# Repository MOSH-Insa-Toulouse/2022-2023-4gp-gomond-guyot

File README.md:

# Projet Capteur
***
<p align="center">

***

## Sommaire
* [1. Description du projet](#PremiereSection)
* [2. Les livrables](#DeuxiemeSection)
* [3. Matériel nécessaire](#TroisiemeSection)
* [4. Simulation](#QuatriemeSection)
* [5. KiCad](#CinquiemeSection)
  * [5.1. Schématique du circuit et création des symboles et empreintes des composants](#CinquiemeSection1)
  * [5.2. Réalisation du PCB et visualisation 3D](#CinquiemeSection2)
* [6. Fabrication du shield](#SixiemeSection)
  * [6.1. Réalisation du PCB](#SixiemeSection1)
  * [6.2. Perçage et soudure](#SixiemeSection2)
* [7. Arduino](#SeptiemeSection)
  * [7.1. Librairies utilisées](#SeptiemeSection1)
  * [7.2. Code Arduino](#SeptiemeSection2)
* [8. Application Android](#HuigtiemeSection)
* [9. Réalisation des tests et résultats](#NeuviemeSection)
  * [9.1. Banc de test](#NeuviemeSection1)
  * [9.2. Résultats](#NeuviemeSection2)
  * [9.3. Pistes d'améliorations](#NeuviemeSection3)
* [10. Datasheet](#DixiemeSection)
* [Contacts](#OnziemeSection)
 
<div id='PremiereSection'/>

## 1. Description du projet 

Ce projet à lieu dans le cadre de l’UF “Du capteur au banc de test” du département de Génie Physique de l’INSA Toulouse. Basé sur l’article "Pencil Drawn Strain Gauges and Chemiresistor on paper" publié sur Scientific Report en 2014, l’objectif de ce projet est de développer un capteur de déformation low-technologie à base de papier et de graphite. En effet, lorsque l’on déforme le papier, la distance entre les particules de graphite déposées au préalable change selon si l’on applique une tension ou une compression. Cette modification de résistance implique une modification de la conductivité de la couche de graphite. On peut ainsi mesurer une variation de résistance que l’on peut relier à la déformation.
Notre objectif était donc de réaliser ce capteur entièrement, c'est-à-dire que nous allions passer par toutes les étapes de sa conception en partant du design et de la fabrication du PCB jusqu’au test du capteur en passant par de la programmation.

<div id='DeuxiemeSection'/>

## 2. Les livrables
Pour ce projet, nous avions différents livrables à rendre avant le 17/05/2023:
- Un shield PCB fonctionnel connecté à une carte Arduino UNO. Le PCB doit nécessairement contenir un amplificateur transimpédance, un capteur bluetooth, un écran OLED. Il peut également contenir un flex sensor, un potentiomètre digital et un encodeur rotatoir. 
- Un code Arduino permettant de gérer le module bluetooth ainsi que les mesures du capteur de déformation. Si présent sur le shield, le code doit aussi prendre en compte l’écran OLED ainsi que l’encodeur rotatoir. 
- Une application Android APK développée à l’aide du site MIT app inventor. 
- Un protocole de calibration du capteur
- Une datasheet du capteur de déformation développé

Dans notre cas, nous avons choisi d'implémenter en plus du capteur Bluetooth et de l’écran OLED sur notre shield, le flex sensor afin de pouvoir comparer notre capteur avec un capteur industriel et l’encodeur rotatoir afin de pouvoir sélectionner différents modes de mesure pour notre capteur. 

<div id='TroisiemeSection'/>

## 3. Matériel nécessaire 
Pour réaliser le capteur ainsi que le PCB associé, voici la liste des composants nécessaires :

* Résistances : 2 de 1 kOhms, 2 de 10 kOhms, 2 de 100 kOhms
* Capacités : 2 de 100 nF, 1 de 1 uF
* Arduino Uno
* Amplificateur opérationnel LTC1050
* Module Bluetooth HC05
* Encodeur rotatoire KY_040
* Ecran OLED 128x64
* Flex Sensor
 
<div id='QuatriemeSection'/>

## 4. Simulation 
Le but de réaliser en amont la simulation LTSpice du circuit intégré au capteur est de vérifier en théorie qu’il a bien été conçu, c’est-à-dire que l’on a un signal de sortie qui correspond à ce que l’on souhaite avoir pour ensuite pouvoir le traiter à l’aide de l’Arduino UNO. On peut l’utiliser également pour vérifier l’impact des différents composants et déterminer les valeurs de résistances, capacités nécessaires pour avoir la tension de sortie souhaitée. Dans notre cas, n’ayant pas conçu le circuit de nous même, nous avons simplement vérifié à l’aide de LTSpice qu’il correspondait à ce dont nous avions besoin pour réaliser pour amplifier le signal du capteur. La version de LTSpice utilisée version utilisée est LTSpice XVII.

Pour cela, nous avons tout d’abord reproduit le circuit sur LTSpice comme montré ci-dessous:

Nous avons ensuite réalisé deux types de simulation: .tran (qui correspond à un signal transient en entrée du circuit) et .ac (qui correspond à un signal continu en entrée du circuit). La première simulation a pour but de vérifier que le signal en sortie V(ADC) du circuit est suffisamment amplifié pour que l’Arduino UNO puisse mesurer sa valeur. On cherche à avoir une tension de l’ordre du Volt. Le circuit est bien conçu puisqu’on observe sur une simulation de 12s que le signal est amplifié jusqu’à 1 Volt.

La seconde simulation est due à la présence de trois filtres passe-bas dans le circuit visant à réduire les bruits parasitant le signal de sortie. En réalisant une simulation .ac nous pouvons ainsi afficher le diagramme de Bode de chaque filtre passe-bas et afin de trouver les fréquences de coupure des différents filtres. Nous avons d’abord vérifié la fréquence de coupure des différents filtres (de 1,6 Hz, 16 Hz et 1,6 kHz) puis vérifié leur efficacité en réalisant une simulation .ac en introduisant un bruit de 50 Hz.

On observe qu’à 50 Hz, le signal est atténué de 78 dB. Le bruit est donc bien filtré.

<div id='CinquiemeSection'/>

## 5. KiCad 
<div id='CinquiemeSection1'/>

### 5.1. Schématique du circuit et création des symboles et empreintes des composants 
La première étape du KICAD a été de réaliser la schématique du circuit, basé sur la simulation réalisée précédemment. Pour cela, nous avons tout d’abord importé le schéma de l’Arduino Uno qui existe déjà sur KiCAD. Nous avons été ensuite amenés à créer les symboles pour les composants non-existants sur LTSpice, ainsi que leur empreinte sur le PCB. La version de KiCad utilisée est KiCad 7.0. Voici ci-dessous les différentes symboles avec leur empreinte associé:

* Amplificateur LTC1050

* Ecran OLED

* Encodeur rotatoire KY_040

* Module bluetooth HC05

* Flex Sensor

Pour les résistances nous avons choisi comme empreinte la Resistor_THT:R_Axial_DIN0204_L3.6mm_D1.6mm_P5.08mm_Horizontal, excepté pour R2 pour laquelle nous avons pris la même empreinte mais à la verticale (elle a donc été placée à la japonaise). Concernant les capacités, C1 et C2 possède comme empreinte Capacitor_THT: C_Disc_D3.0mm_W1.6mm_P2.50mm, tandis que C4 a pour empreinte Capacitor_THT:C_Rect_L7.0mm_W4.5mm_P5.00mm.

Voici ci-dessous le schéma de la schématique du circuit réalisé sur KiCAD:

<p align="center">

<div id='CinquiemeSection2'/>

### 5.2. Réalisation du PCB et visualisation 3D 
Pour le PCB, nous avions pour contrainte de n’imprimer que sur une seule face. Il a donc fallu optimiser autant que possible les connexions entre les différents composés afin de limiter la présence de PADs. Nous avons réussi à n’avoir besoin que d'un seul PAD sur notre PCB, qui, n’ayant pas de face arrière, s’est traduit par la connexion du PAD à l’aide d’un fil de résistance. Voici ci-dessous l’empreinte du PCB réalisé:

<p align="center">

Le plan en bleu est le plan de masse. Les PADS sont de formes circulaires de 2mm de diamètre avec une forme de perçage circulaire de 1mm pour l’Arduino et le capteur de déformation et 0,8mm pour le reste. Les largeurs de pistes sont de 1mm et l’isolation entre les pistes et le plan de masse est de 0,3mm. Nous avons choisi ces derniers paramètres afin de faciliter l’étape de soudure.
	
Afin de visualiser en 3D notre composant et pouvoir voir la place que prend chaque composant, nous avons dû, pour les empreintes que nous avons créées, utiliser le site internet GrabCADafin de récupérer le fichier 3D de nos composants. Voici-ci dessous la visualisation 3D du PCB réalisé: 
	
<p align="center">

<div id='SixiemeSection'/>

## 6. Fabrication du shield 
<div id='SixiemeSection1'/>

### 6.1. Réalisation du PCB 

Le PCB a été réalisé par Catherine CROUZET du département du Génie Physique de l’INSA Toulouse à l’aide du matériel du département du Génie Physique et du département	Électrique et Informatique. Avant impression, l’empreinte du PCB a été vérifiée par Mme CROUZET qui a ensuite imprimé sur papier le calque de modélisation issu du PCB réalisé sur KiCAD.
 Nous sommes parti d’une plaquette d'époxy couverte d’une couche de cuivre d’environ  60µm sur laquelle nous avons appliqué notre calque qui a permis de tracer les pistes sur la plaquette du PCB à l’aide d’une insolation UV. Une fois les pistes tracées, elles sont ensuite révélées à l’aide d’un révélateur qui après quelques minutes, retire la résine non éclairée pas les UV. La plaquette est ensuite placée dans un bain de perchlorure de fer pendant 7 minutes afin de réaliser la gravure du PCB. Lors de cette étape, le cuivre non protégé par la résine est retiré. Nous obtenons alors le PCB comme désigné sur KiCAD. On applique pour terminer un peu d’acétone afin de retirer les dernières traces de résines encore présentes.

 <div id='SixiemeSection2'/>

### 6.2. Perçage et soudure 
Une fois les pistes du PCB créées, il faut réaliser le perçage du PCB puis la soudure des composants. Pour cela nous avons utilisé la perceuse électrique mise à disposition aux étudiants du Génie Physique. Les tailles de forêts ont été choisies en fonction des tailles de trous de perçage designé sur KiCAD (c’est à dire 0,8mm ou 1mm de diamètre selon les composants). Une fois tous les composants soudés sur la face avant, nous avons pu connecter le PCB à l’Arduino Uno. 

<div id='SeptiemeSection'/>

## 7. Arduino 
<div id='SeptiemeSection1'/>

### 7.1. Librairies utilisées 
Nous avons utiliser la vertion de Arduino IDE 2.1.0.
Pour la réalisation du code Arduino nous avons utiliser deux librairies qui sont **"SoftwareSerial.h"** pour réaliser un software serial sur deux pin pour l'utilisation du modude bluetooth. La deuxième est **"Adafruit_SSD1306.h"** qui sert pour l'utilisation de l'écran OLED.

<div id='SeptiemeSection2'/>

### 7.2. Code Arduino 
Nous avons réaliser deux code Arduino dans ce projet. Le premier permet de controler le capteur et tout ces composants. Le deuxième sert lors de la procédure de calibration.

#### Code pour le Capteur 
Ce [code](https://github.com/MOSH-Insa-Toulouse/2022-2023-4gp-gomond-guyot/blob/main/arduino/Programme_finaleVFinale.ino) est le coeur du fonctionnement du capteur. 
-Il permet tout d'abord récupérer les valeurs de tension en sortie de l'amplificateur et de réaliser les différents calculs pour retrouver la résistance de notre capteur.
-Il permet également le contrôle et l'utilisaton des différents éléments ajoutés sur le shield:
	
   * il y a le **module Bluetooth** qui permet d'envoyer la valeur de tension lue et de l'envoyer à l'application Android.
	
   * il y a **l'encodeur rotatoir** où nous avons grâce à lui réaliser trois menus en fonction d'où l'on se trouve dans la plage de valeurs de l'encodeur. Il y a un menu avec un mode de lecteur continu de la résistance, un autre mode qui réalise une moyenne sur 200 valeurs de la résistance et n mode pour afficher la lecture du flex sensor. Tout ces menus sont visible sur l'écran OLED.
	
   * il y a **l'écran OLED** qui permet d'afficher la valeur de la résistance de notre capteur ou du flex sensor en fonction du menu que nous avons choisi. Le menu où nous sommes est également affiché.

#### Code pour la calibration
Ce [code](https://github.com/MOSH-Insa-Toulouse/2022-2023-4gp-gomond-guyot/blob/main/arduino/programme_calibration.ino) permet de contrôler un Servo-Moteur qui va se positionner à différent angles déterminés (0, 30, 60, 90, 120). Il va attendre 2 secondes à chaques position pour nous permettre de lire la valeur. La procédure est activée grâce à un bouton poussoir et pendant que le servo-moteur est en mouvement une LED est allumée.

<div id='HuigtiemeSection'/>

## 8. Application Android 
Nous avons développé une application Android fonctionnant à l’aide du module Bluetooth HC-05. L’application se présente comme ci-dessous: 

<p align="center">

L’application possède un menu de sélection bluetooth permettant de choisir à quel module bluetooth se connecter. Une fois connecté, le code Arduino envoie via le module la valeur de tension en sortie du circuit V(ADC) en Volt sous forme d’un byte à l’application. L’application convertit ces valeurs tout d’abord en float, puis en résistance en M𝛺 à l’aide de la formule: 

<p align="center">
	
Le schéma fonctionnel du programme derrière l’application est visible sous ce lien: [LIEN APK](https://github.com/MOSH-Insa-Toulouse/2022-2023-4gp-gomond-guyot/blob/main/app/Application_Projet.aia)

<div id='NeuviemeSection'/>

## 9. Réalisation des tests et résultats 
<div id='NeuviemeSection1'/>

### 9.1. Banc de test 
Pour réaliser les différents tests de calibration nous avons réaliser deux bancs de tests pour avoir une calibration en fonction de la déformation et en fonction de l'angle. Nous avons réaliser les deux calibrations car nous avons trouvé, sur le point physique, intéressant de la réaliser en fonction de la déformation de la couche de graphite. Mais sur l'aspect utilisation du capteur, il est plus utile et intéressant de connaitre la résistance en fonction de l'angle que fait le capteur.

#### Banc de test pour la calibration en fonction de la deformation
Pour cette methode nous avons découpé des cercles de différents rayons de courbure (1, 2, 4 et 6 cm) comme montrée ci dessous.

<p align="center">
	
Ce rayon de courbure nous permet de remonter à la déformation ε gracce à la formule suivante qui est expliqué par le shéma ci-dessous.

#### Banc de test pour la calibration en fonction de l'angle
Pour cette methode nous avons utilisé un module en bois  qui était fournis par le département ainsi qu'un servo-moteur. Nous utilisons le code décrit à la partie 7.2 pour la calibration. Le servo-moteur tord le capteur à différents angles prédéfinis.

<div id='NeuviemeSection2'/>

### 9.2. Résultats
Les résultats complets ont été réalisé sur Exel dans le dossier [result.](https://github.com/MOSH-Insa-Toulouse/2022-2023-4gp-gomond-guyot/blob/main/result/calcules_deformation.xlsx) Sinon voici les différentes courbes de calibration en fonction de l'angle et de la déformation.
Nous avons réalisé les mesures en fonction de la déformation en compression et en tension. Pour les mesures en fonction de l'angle, nous avons réalisé seulement la compression car les résultats que nous avons obtenu en tension n'était pas exploitables.

* Variation de la résistance en fonction de la deformation (tension)

* Variation de la résistance en fonction de la deformation (compression)

* Variation de la résistance en fonction de l'angle (compression)

Quand nous travaillons en tension, la monocouche de graphite déposé sur le papier va s'étirer ce qui va augmenter la distance entre les différents atomes de Carbone et ainsi augmenter la résitance du capteur.
Lorsque nous travaillons en tension, il se passe l'opposé. Les atomes de Carbone vont se rapprocher et la résistance du capteur va diminuer.
En fonction du type de crayon utilisé, les variations relatives de résistance changent. En effet, plus le crayon est gras, c'est à dire qu'il dépose plus de graphite, moins sa variation relative de résistance est élevée. Nous pouvons vérifier cela sur les différentes courbes que nous avons obtenu.

<div id='NeuviemeSection3'/>
 
### 9.3. Pistes d'améliorations
Plusieurs pistes d’améliorations pour ce capteur sont possibles. Tout d’abord, comme nous avons pu l’expérimenter, la répétabilité du capteur est peu fiable dû à plusieurs facteurs:

-Le dépôt de la quantité de graphite n’est pas contrôlée, et cette quantité diminue au cours du temps avec l’air alentour.

-Le papier s’use assez rapidement et ne peut pas supporter des déformations trop importantes.

Ainsi, on pourrait essayer de réaliser une méthode afin de déposer une quantité contrôlée de graphite sur le papier, ainsi que choisir un papier plus élastique. 
Un autre ajout possible sur la partie hardware du capteur serait le potentiomètre digital qui permettrait d’adapter la tension de sortie du capteur en fonction de la résistance du capteur. 
La partie banc de tests pourrait être améliorée en réalisant des tests sur des cylindres solides imprimés en 3D et avec plus de tailles différentes afin d’obtenir plus de données pour tracer nos courbes.

#### Comparaison avec le Flex-Sensor SEN-10264

*Variation de la résistance du flex sensor en compression

Pour comparer la sensibilité des deux capteurs, nous pouvons comparer les coefficients directeur du flex sensor avec celui du capteur de contrainte HB sur la compression. Pour le flex sensor, nous avons obtenu un coefficient de -2.27/° tandis que pour le capteur de contrainte HB nous avons -0.24/°. On peu donc dire que le flex sensor est beaucoup plus sensible à la déformation que notre capteur de contrainte en graphite. Le flex sensor pourrait être plus utile pour detecter de petites déformations grâce à sa plus grande sensibilité. A coté de cela, notre capteur en graphite à plus de difficulté à détecter les petites déformation où les petit angles. Il serait plus utile pour savoir s'il est plié ou non.

<div id='DixiemeSection'/>

## 10. Datasheet
La datasheet du capteur est disponible [ici](https://github.com/MOSH-Insa-Toulouse/2022-2023-4gp-gomond-guyot/blob/main/Datasheet.pdf)

<div id='OnziemeSection'/>

## Contacts 
Nous sommes disponibles pour toute question sur le projet, n'hesitez pas à nous contacter.

-GUYOT Adrien : aguyot@etud.insa-toulouse.fr

-GOMOND François : fgomond@insa-toulouse.fr

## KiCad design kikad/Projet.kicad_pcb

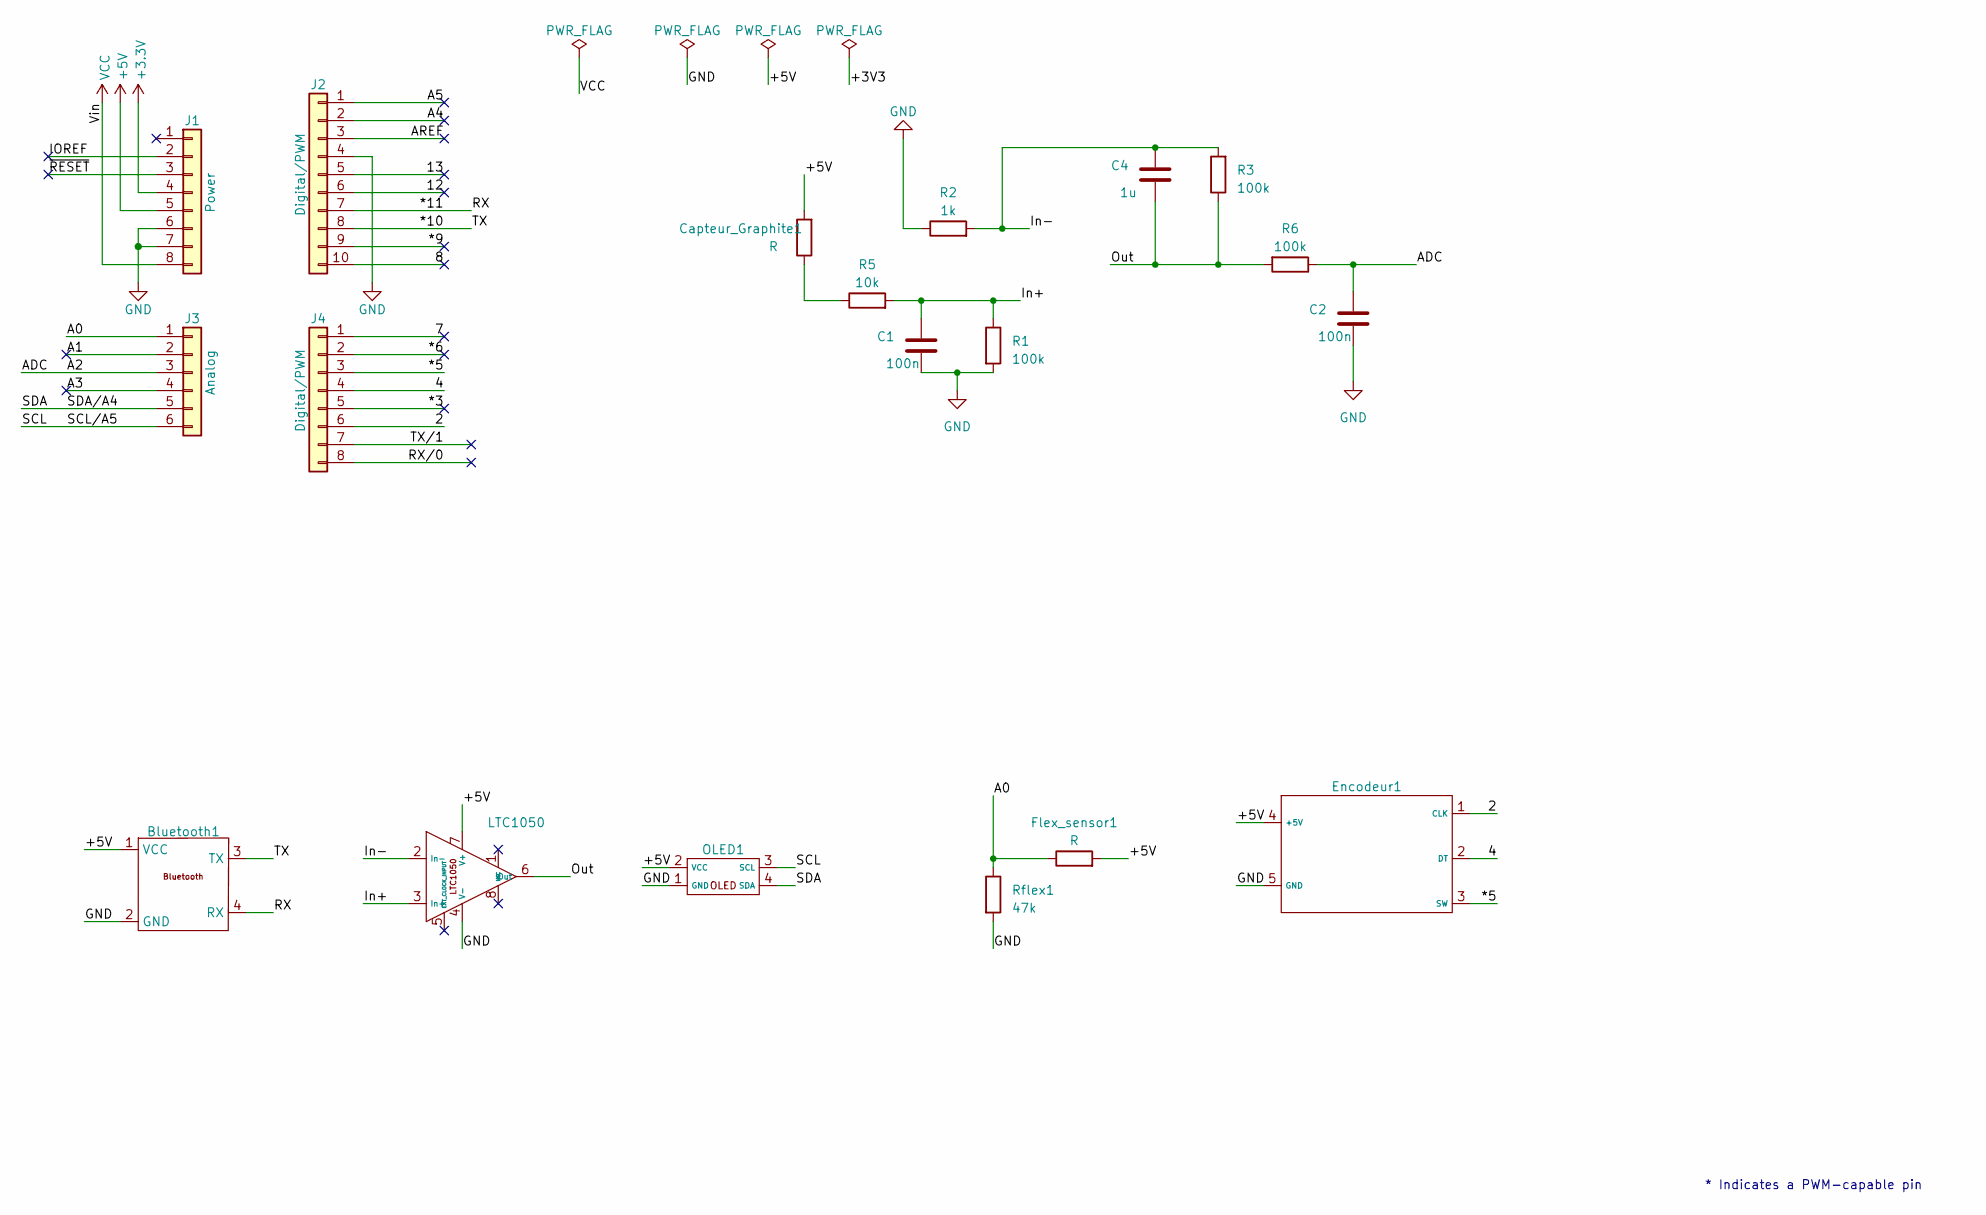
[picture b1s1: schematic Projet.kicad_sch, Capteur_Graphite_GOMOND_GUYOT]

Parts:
Bluetooth1: Bluetooth
C1, C2: 100n; C_Disc_D3.0mm_W1.6mm_P2.50mm
C4: 1u; C_Rect_L7.0mm_W4.5mm_P5.00mm
Capteur_Graphite1: R; PinSocket_1x02_P2.54mm_Vertical
Encodeur1: Encodeur
Flex_sensor1: R; PinSocket_1x02_P2.54mm_Vertical
J1: Power; PinSocket_1x08_P2.54mm_Vertical
J2: Digital/PWM; PinSocket_1x10_P2.54mm_Vertical
J3: Analog; PinSocket_1x06_P2.54mm_Vertical
J4: Digital/PWM; PinSocket_1x08_P2.54mm_Vertical
LTC1050: LTC1050
OLED1: OLED
R1, R3, R6: 100k; R_Axial_DIN0204_L3.6mm_D1.6mm_P5.08mm_Horizontal
R2: 1k; R_Axial_DIN0204_L3.6mm_D1.6mm_P2.54mm_Vertical
R5: 10k; R_Axial_DIN0204_L3.6mm_D1.6mm_P5.08mm_Horizontal
Rflex1: 47k; R_Axial_DIN0204_L3.6mm_D1.6mm_P5.08mm_Horizontal

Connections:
+3V3: J1.4
+5V: Bluetooth1.1 (VCC), Capteur_Graphite1.2, Encodeur1.4 (+5V), Flex_sensor1.2, J1.5, LTC1050.7 (V+), OLED1.2 (VCC)
/2: Encodeur1.1 (CLK), J4.6
/4: Encodeur1.2 (DT), J4.4
/7: J4.1
/8: J2.10
/12: J2.6
/13: J2.5
/*3: J4.5
/*5: Encodeur1.3 (SW), J4.3
/*6: J4.2
/*9: J2.9
/*10: Bluetooth1.3 (TX), J2.8
/*11: Bluetooth1.4 (RX), J2.7
/A0: Flex_sensor1.1, J3.1, Rflex1.1
/A1: J3.2
/A2: C2.2, J3.3, R6.1
/A3: J3.4
/A4: J2.2
/A5: J2.1
/AREF: J2.3
/IOREF: J1.2
/In+: C1.2, LTC1050.3 (In+), R1.1, R5.2
/In-: C4.2, LTC1050.2 (In-), R2.2, R3.2
/Out: C4.1, LTC1050.6 (Out), R3.1, R6.2
/RX/0: J4.8
/SCL: J3.6, OLED1.3 (SCL)
/SDA: J3.5, OLED1.4 (SDA)
/TX/1: J4.7
/~RESET: J1.3
GND: Bluetooth1.2 (GND), C1.1, C2.1, Encodeur1.5 (GND), J1.6, J1.7, J2.4, LTC1050.4 (V-), OLED1.1 (GND), R1.2, R2.1, Rflex1.2
unnamed: Capteur_Graphite1.1, R5.1
VCC: J1.8

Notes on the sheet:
* Indicates a PWM-capable pin

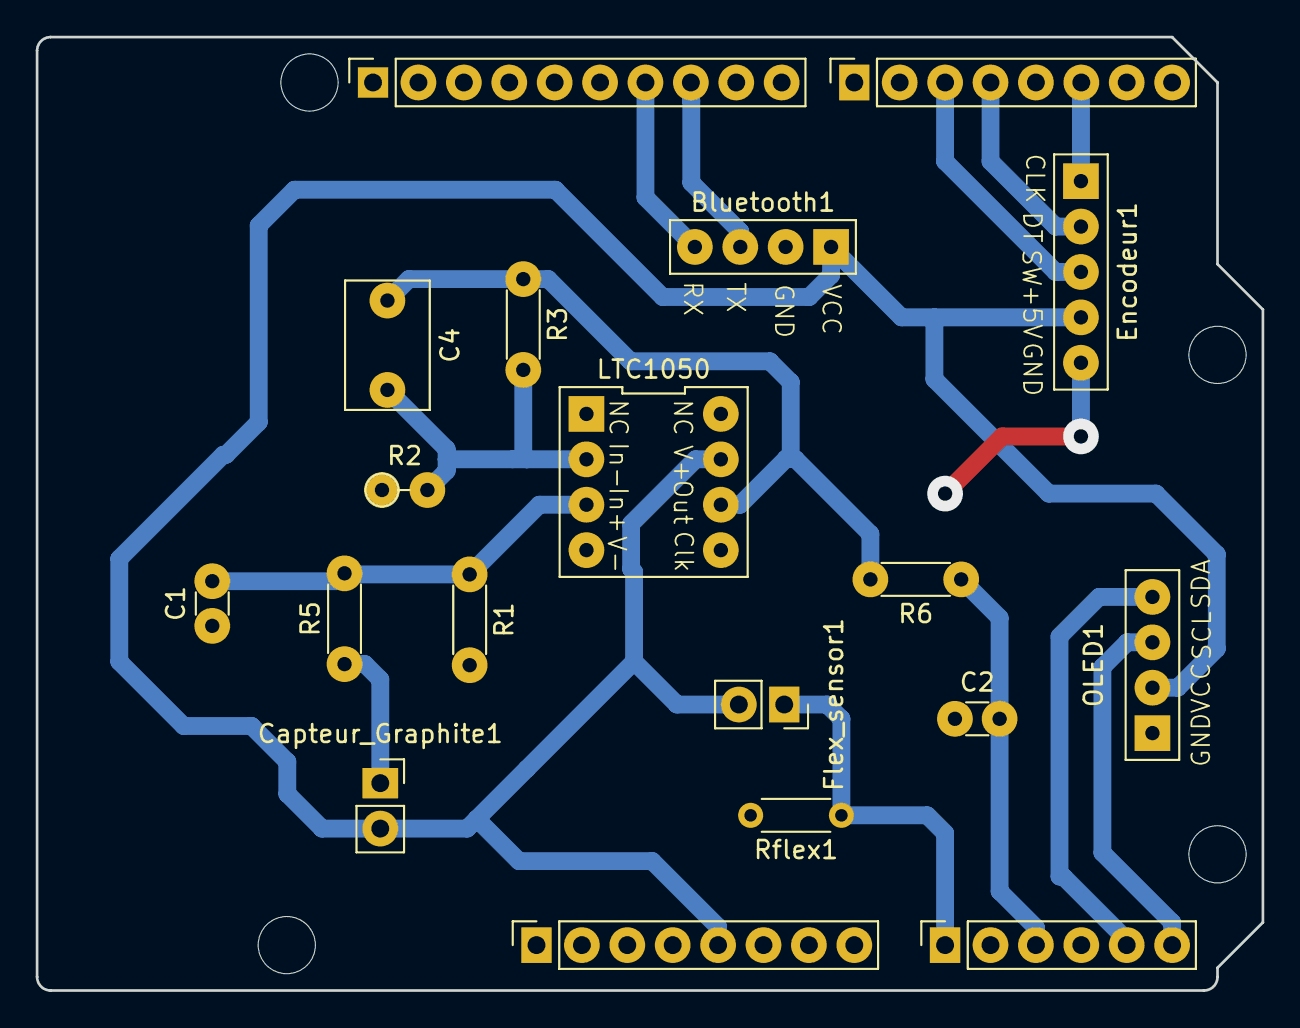
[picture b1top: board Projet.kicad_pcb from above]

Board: 2 copper layers, 68.6 x 53.3 mm, 23 parts (0 on the bottom side), 15 nets.

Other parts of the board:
MH1, MH2, MH3, MH4: MountingHole_3.2mm

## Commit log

2023-02-01 TO DO LIST
2023-02-01 add chemin
2023-02-01 add space
2023-03-01 Kicad Bluetooth all files
    (on previous upload some files were missing)
2023-04-27 doss
